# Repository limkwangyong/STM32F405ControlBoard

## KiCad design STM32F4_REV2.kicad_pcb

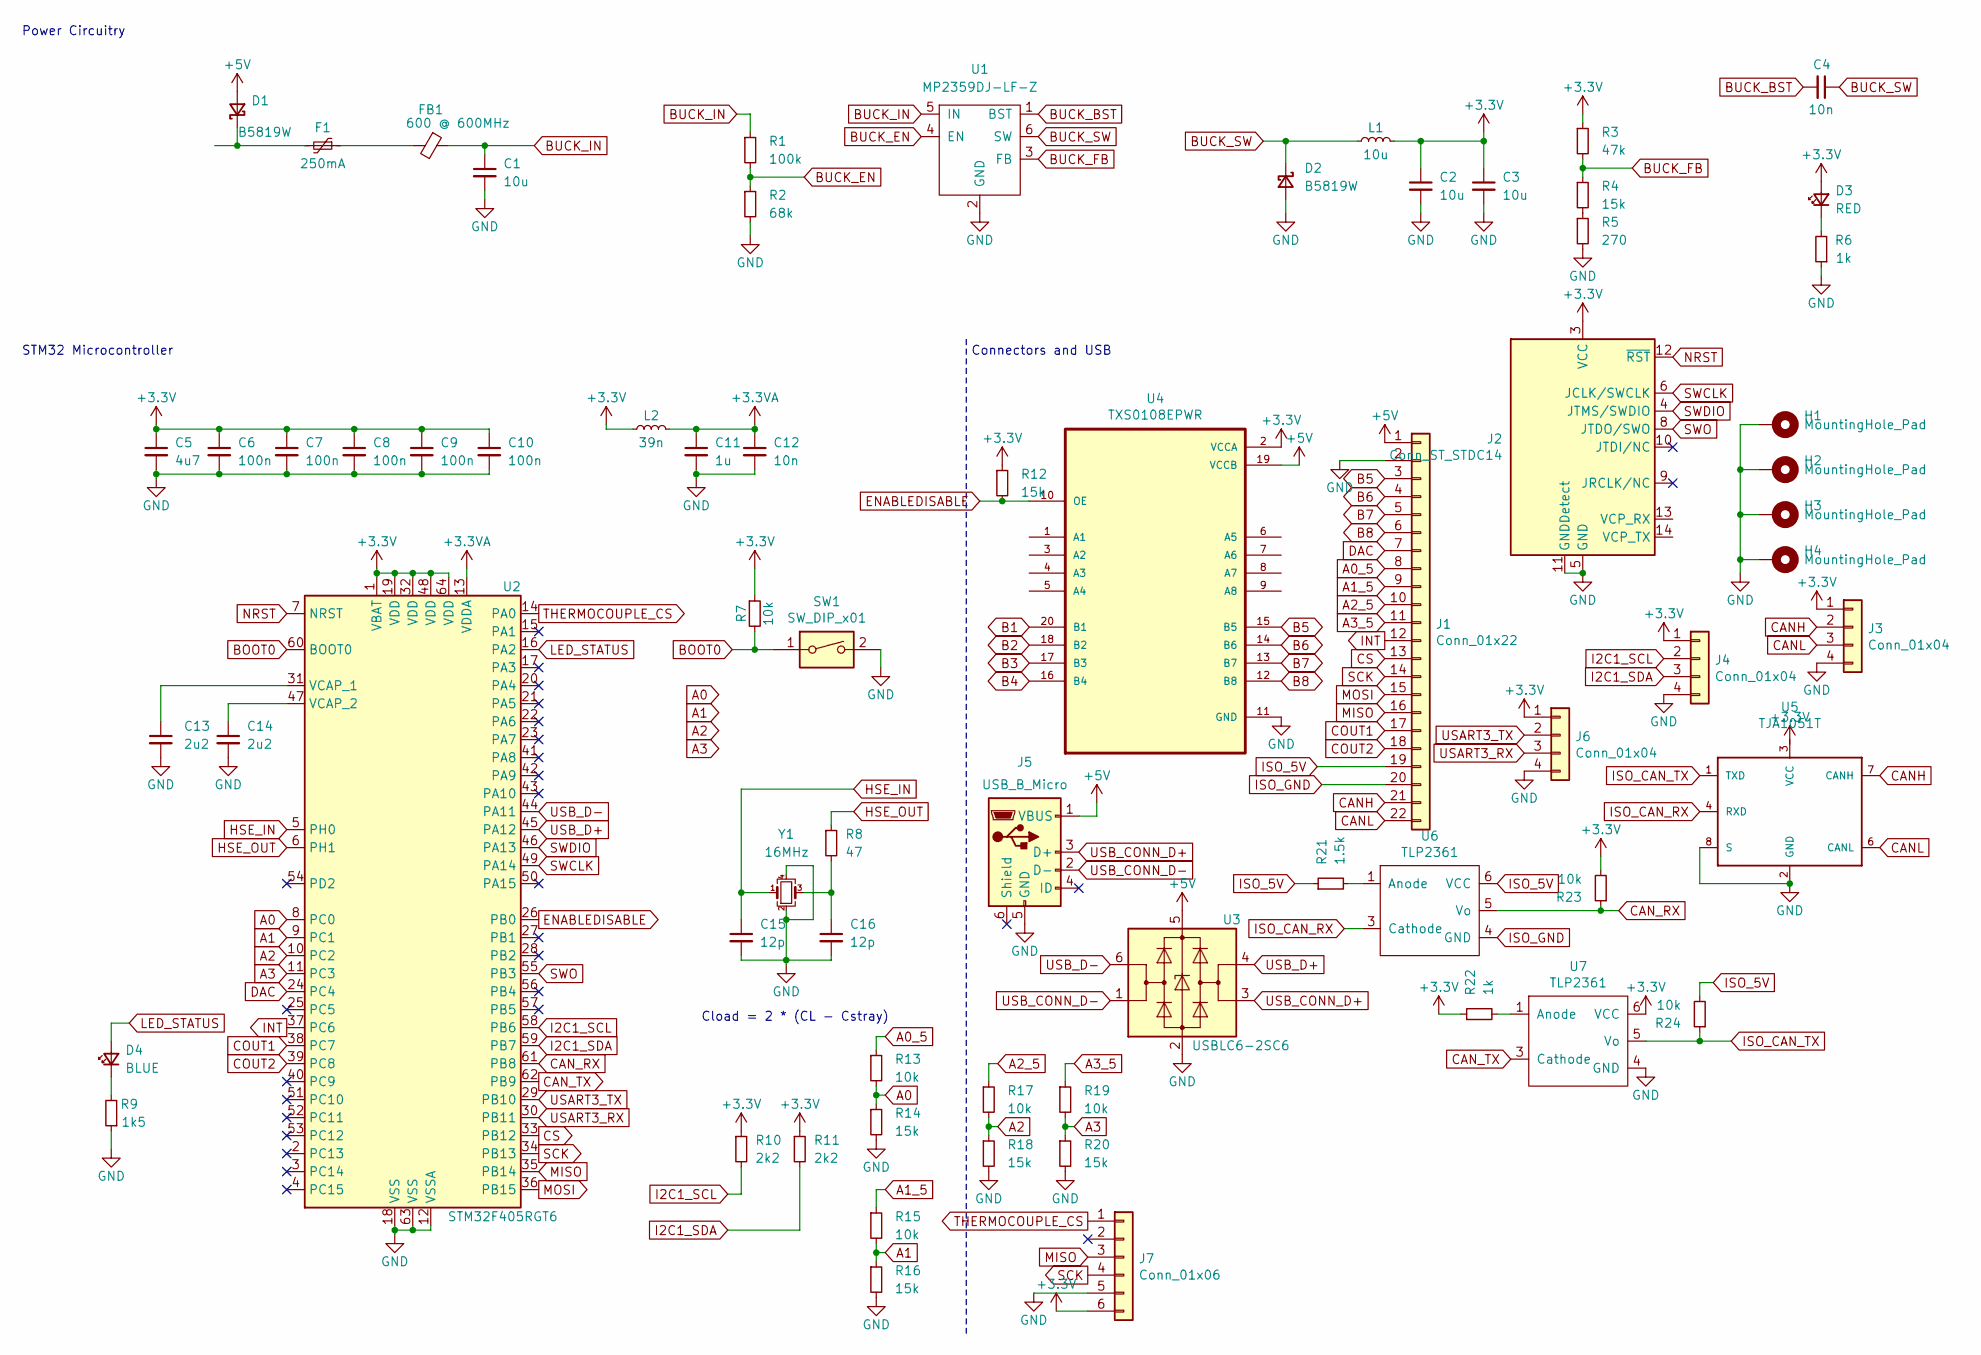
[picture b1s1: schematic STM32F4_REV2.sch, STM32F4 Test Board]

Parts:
C1, C2, C3: 10u; C_1206_3216Metric; LCSC Part # C13585
C4: 10n; C_0603_1608Metric; LCSC Part # C57112
C5: 4u7; C_0603_1608Metric; LCSC Part # C19666
C6, C7, C8, C9, C10: 100n; C_0402_1005Metric; LCSC Part # C1525
C11: 1u; C_0402_1005Metric; LCSC Part # C52923
C12: 10n; C_0402_1005Metric; LCSC Part # C15195
C13, C14: 2u2; C_0603_1608Metric; LCSC Part # C23630
C15, C16: 12p; C_0402_1005Metric; LCSC Part # C1547
D1, D2: B5819W; D_SOD-123; LCSC Part # C8598
D3: RED; LED_0603_1608Metric; LCSC Part # C2286
D4: BLUE; LED_0603_1608Metric; LCSC Part # C72041
F1: 250mA; Fuse_1206_3216Metric; LCSC Part # C369159
FB1: 600 @ 600MHz; L_0805_2012Metric; LCSC Part # C1017
H1, H2, H3, H4: MountingHole_Pad; MountingHole_4.3mm_M4_Pad_Via
J1: Conn_01x22; PinHeader_1x22_P2.54mm_Horizontal
J2: Conn_ST_STDC14; PinHeader_2x07_P1.27mm_Vertical_SMD
J3, J4, J6: Conn_01x04; PinHeader_1x04_P2.54mm_Vertical
J5: USB_B_Micro; USB_Micro-B_Molex_47346-0001
J7: Conn_01x06; PinHeader_1x06_P2.54mm_Vertical
L1: 10u; L_Sunlord_MWSA0518_5.4x5.2mm; LCSC Part # C139506
L2: 39n; L_0402_1005Metric; LCSC Part # C26443
R1: 100k; R_0603_1608Metric; LCSC Part # C25803
R2: 68k; R_0603_1608Metric; LCSC Part # C23231
R3: 47k; R_0603_1608Metric; LCSC Part # C25819
R4, R12: 15k; R_0603_1608Metric; LCSC Part # C22809
R5: 270; R_0603_1608Metric; LCSC Part # C22966
R6: 1k; R_0603_1608Metric; LCSC Part # C21190
R7: 10k; R_0402_1005Metric; LCSC Part # C25744
R8: 47; R_0402_1005Metric; LCSC Part # C25118
R9: 1k5; R_0603_1608Metric; LCSC Part # C22843
R10, R11: 2k2; R_0402_1005Metric; LCSC Part # C25879
R13, R15, R17, R19, R23, R24: 10k; R_0603_1608Metric; LCSC Part # C22966
R14, R16, R18, R20: 15k; R_0603_1608Metric; LCSC Part # C22966
R21: 1.5k; R_0603_1608Metric; LCSC Part # C22966
R22: 1k; R_0603_1608Metric; LCSC Part # C22966
SW1: SW_DIP_x01; SW_DIP_SPSTx01_Slide_6.7x4.1mm_W6.73mm_P2.54mm_LowProfile_J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
U1: MP2359DJ-LF-Z; SOT-23-6; LCSC Part # C14259
U2: STM32F405RGT6; LQFP-64_10x10mm_P0.5mm; LCSC Part # C15742
U3: USBLC6-2SC6; SOT-23-6; LCSC Part # C7519
U4: TXS0108EPWR; SOP65P640X120-20N
U5: TJA1051T; SOT96-1
U6, U7: TLP2361; SOIC-6-5_W4.55mm
Y1: 16MHz; Oscillator_SMD_Abracon_ASE-4Pin_3.2x2.5mm; LCSC Part # C13738

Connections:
+3.3VA: C11.1, C12.1, L2.2, U2.13 (VDDA)
+3V3: C2.1, C3.1, C5.1, C6.1, C7.1, C8.1, C9.1, C10.1, D3.2 (A), J2.3 (VCC), J3.1, J4.1, J6.1, J7.6, L1.2, L2.1, R3.1, R7.1, R10.1, R11.1, R12.1, R22.1, R23.2, U2.1 (VBAT), U2.19 (VDD), U2.32 (VDD), U2.48 (VDD), U2.64 (VDD), U4.2 (VCCA), U7.6 (VCC)
+5V: D1.2 (A), J1.1, J5.1 (VBUS), U3.5 (VBUS), U4.19 (VCCB)
A0: R13.2, R14.1, U2.8 (PC0)
A0_5: J1.8, R13.1
A1: R15.2, R16.1, U2.9 (PC1)
A1_5: J1.9, R15.1
A2: R17.2, R18.1, U2.10 (PC2)
A2_5: J1.10, R17.1
A3: R19.2, R20.1, U2.11 (PC3)
A3_5: J1.11, R19.1
B1: U4.20 (B1)
B2: U4.18 (B2)
B3: U4.17 (B3)
B4: U4.16 (B4)
B5: J1.3, U4.15 (B5)
B6: J1.4, U4.14 (B6)
B7: J1.5, U4.13 (B7)
B8: J1.6, U4.12 (B8)
BOOT0: R7.2, SW1.1, U2.60 (BOOT0)
BUCK_BST: C4.2, U1.1 (BST)
BUCK_EN: R1.2, R2.1, U1.4 (EN)
BUCK_FB: R3.2, R4.1, U1.3 (FB)
BUCK_IN: C1.1, FB1.1, R1.1, U1.5 (IN)
BUCK_SW: C4.1, D2.1 (K), L1.1, U1.6 (SW)
CANH: J1.21, J3.2, U5.7 (CANH)
CANL: J1.22, J3.3, U5.6 (CANL)
CAN_RX: R23.1, U2.61 (PB8), U6.5 (Vo)
CAN_TX: U2.62 (PB9), U7.3 (Cathode)
COUT1: J1.17, U2.38 (PC7)
COUT2: J1.18, U2.39 (PC8)
CS: J1.13, U2.33 (PB12)
DAC: J1.7, U2.24 (PC4)
ENABLEDISABLE: R12.2, U2.26 (PB0), U4.10 (OE)
GND: C1.2, C2.2, C3.2, C5.2, C6.2, C7.2, C8.2, C9.2, C10.2, C11.2, C12.2, C13.2, C14.2, C15.2, C16.2, D2.2 (A), H1.1, H2.1, H3.1, H4.1, J1.2, J2.5 (GND), J2.7 (GND), J2.11 (GNDDetect), J3.4, J4.4, J5.5 (GND), J6.4, J7.5, R2.2, R5.2, R6.1, R9.1, R14.2, R16.2, R18.2, R20.2, SW1.2, U1.2 (GND), U2.12 (VSSA), U2.18 (VSS), U2.63 (VSS), U3.2 (GND), U4.11 (GND), U5.2 (GND), U5.8 (S), U7.4 (GND), Y1.2, Y1.4
HSE_IN: C15.1, U2.5 (PH0), Y1.1
HSE_OUT: R8.1, U2.6 (PH1)
I2C1_SCL: J4.2, R10.2, U2.58 (PB6)
I2C1_SDA: J4.3, R11.2, U2.59 (PB7)
INT: J1.12, U2.37 (PC6)
ISO_5V: J1.19, R21.1, R24.2, U6.6 (VCC)
ISO_CAN_RX: U5.4 (RXD), U6.3 (Cathode)
ISO_CAN_TX: R24.1, U5.1 (TXD), U7.5 (Vo)
ISO_GND: J1.20, U6.4 (GND)
LED_STATUS: D4.2 (A), U2.16 (PA2)
MISO: J1.16, J7.3, U2.35 (PB14)
MOSI: J1.15, U2.36 (PB15)
NRST: J2.12 (~RST), U2.7 (NRST)
unnamed: C13.1, U2.31 (VCAP_1)
unnamed: C14.1, U2.47 (VCAP_2)
unnamed: C16.1, R8.2, Y1.3
unnamed: D1.1 (K), F1.2
unnamed: D3.1 (K), R6.2
unnamed: D4.1 (K), R9.2
unnamed: F1.1, FB1.2
unnamed: R4.2, R5.1
unnamed: R21.2, U6.1 (Anode)
unnamed: R22.2, U7.1 (Anode)
SCK: J1.14, J7.4, U2.34 (PB13)
SWCLK: J2.6 (JCLK/SWCLK), U2.49 (PA14)
SWDIO: J2.4 (JTMS/SWDIO), U2.46 (PA13)
SWO: J2.8 (JTDO/SWO), U2.55 (PB3)
THERMOCOUPLE_CS: J7.1, U2.14 (PA0)
USART3_RX: J6.3, U2.30 (PB11)
USART3_TX: J6.2, U2.29 (PB10)
USB_CONN_D+: J5.3 (D+), U3.3 (I/O2)
USB_CONN_D-: J5.2 (D-), U3.1 (I/O1)
USB_D+: U2.45 (PA12), U3.4 (I/O2)
USB_D-: U2.44 (PA11), U3.6 (I/O1)

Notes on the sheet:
Cload = 2 * (CL - Cstray)
STM32 Microcontroller
Power Circuitry
Connectors and USB

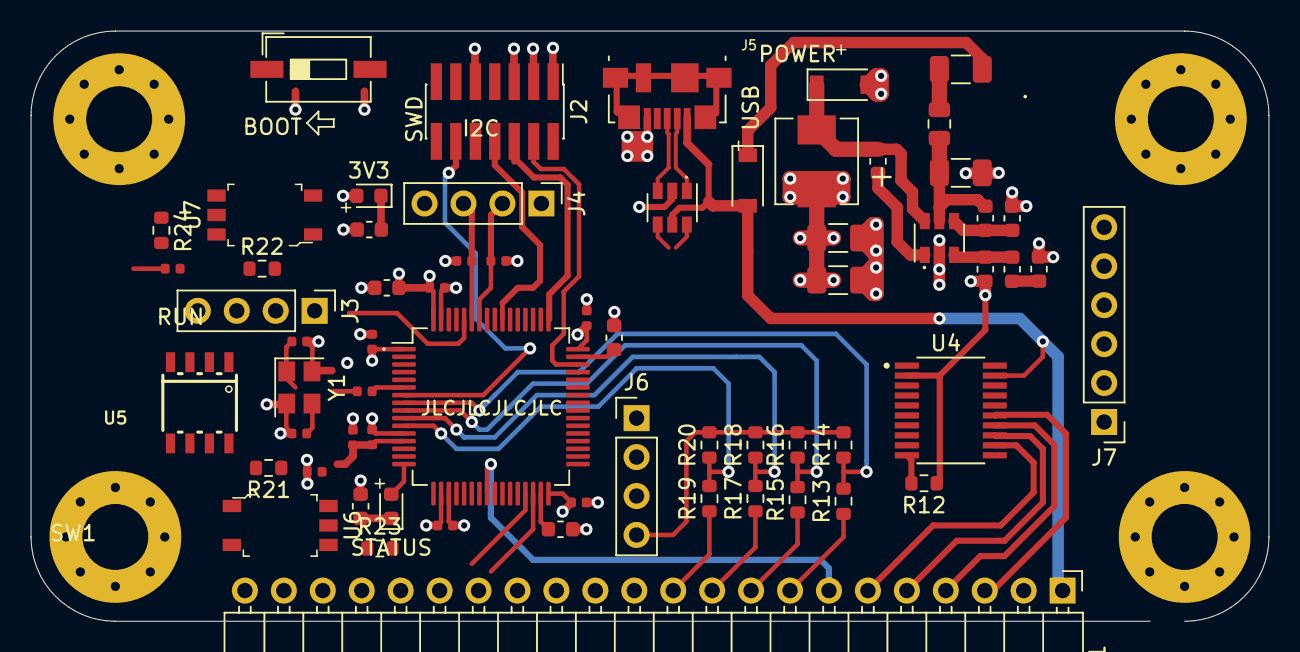
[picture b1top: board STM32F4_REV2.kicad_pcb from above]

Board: 4 copper layers, 80.8 x 38.5 mm, 68 parts (0 on the bottom side), 65 nets.

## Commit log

2021-06-30 Updated the schematics and PCB
2021-07-06 Added some datasheets for thermocouple and updated schematics and PCB
